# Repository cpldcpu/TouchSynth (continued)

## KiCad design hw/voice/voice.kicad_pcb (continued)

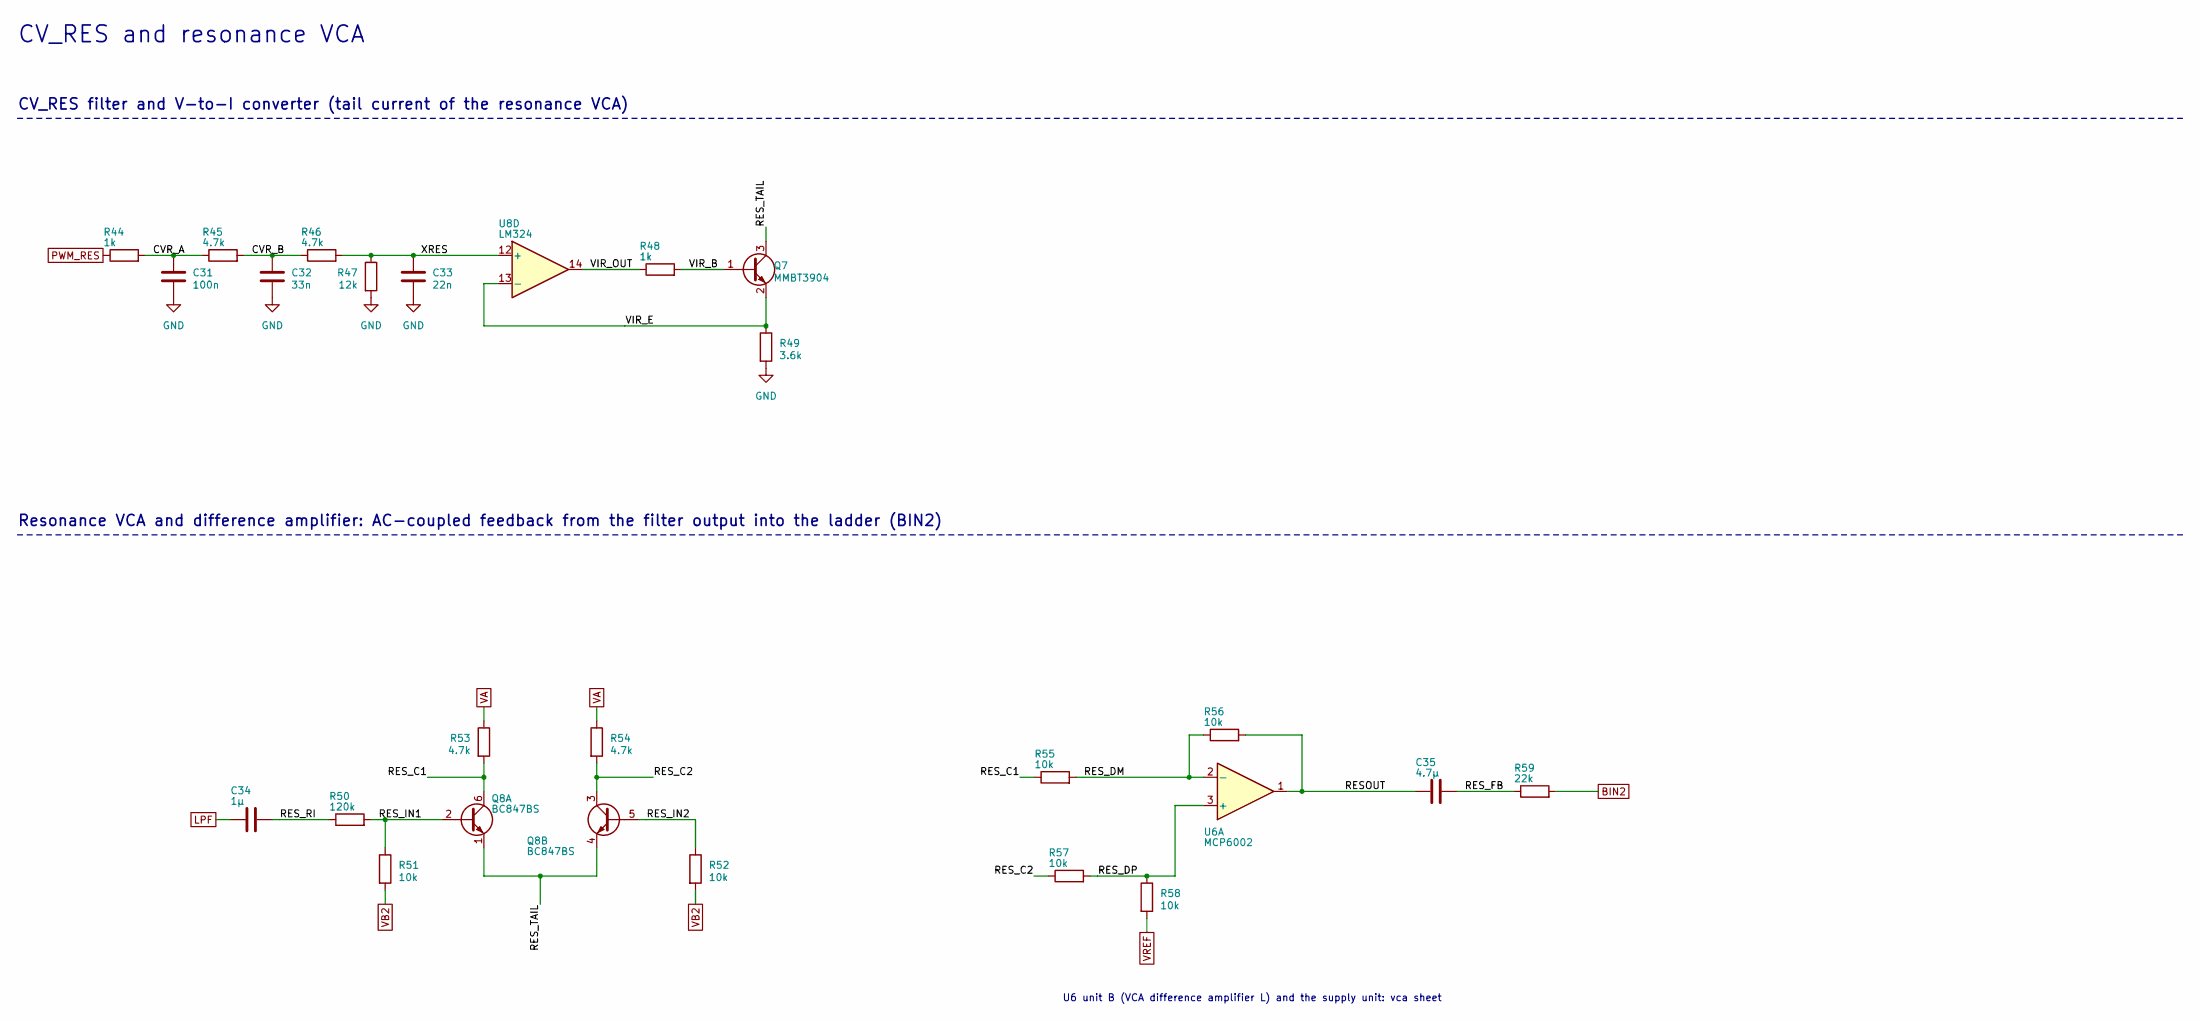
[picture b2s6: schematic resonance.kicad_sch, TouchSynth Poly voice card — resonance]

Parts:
C31: 100n; C_0402_1005Metric; LCSC C1525
C32: 33n; C_0603_1608Metric; LCSC C21117
C33: 22n; C_0402_1005Metric; LCSC C1532
C34: 1µ; C_0402_1005Metric; LCSC C52923
C35: 4.7µ; C_0402_1005Metric; LCSC C23733
Q7: MMBT3904; SOT-23; LCSC C20526
Q8: BC847BS; SOT-363_SC-70-6; LCSC C41375126
R44, R48: 1k; R_0402_1005Metric; LCSC C11702
R45, R46, R53, R54: 4.7k; R_0402_1005Metric; LCSC C25900
R47: 12k; R_0402_1005Metric; LCSC C25752
R49: 3.6k; R_0603_1608Metric; LCSC C22980
R50: 120k; R_0402_1005Metric; LCSC C25750
R51, R52, R55, R56, R57, R58: 10k; R_0402_1005Metric; LCSC C25744
R59: 22k; R_0402_1005Metric; LCSC C25768
U6: MCP6002; SOIC-8_3.9x4.9mm_P1.27mm; LCSC C7377
U8: LM324; SOIC-14_3.9x8.7mm_P1.27mm; LCSC C71035

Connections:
/resonance/CVR_A: C31.1, R44.2, R45.1
/resonance/CVR_B: C32.1, R45.2, R46.1
/resonance/RESOUT: C35.1, R56.2, U6.1
/resonance/RES_C1: Q8.6 (C1), R53.2, R55.1
/resonance/RES_C2: Q8.3 (C2), R54.2, R57.1
/resonance/RES_DM: R55.2, R56.1, U6.2 (-)
/resonance/RES_DP: R57.2, R58.1, U6.3 (+)
/resonance/RES_FB: C35.2, R59.1
/resonance/RES_IN1: Q8.2 (B1), R50.2, R51.1
/resonance/RES_IN2: Q8.5 (B2), R52.1
/resonance/RES_RI: C34.2, R50.1
/resonance/RES_TAIL: Q7.3 (C), Q8.1 (E1), Q8.4 (E2)
/resonance/VIR_B: Q7.1 (B), R48.2
/resonance/VIR_E: Q7.2 (E), R49.1, U8.13 (-)
/resonance/VIR_OUT: R48.1, U8.14
/resonance/XRES: C33.1, R46.2, R47.1, U8.12 (+)
BIN2: R59.2; also elsewhere on the board
GND: C31.2, C32.2, C33.2, R47.2, R49.2; also elsewhere on the board
LPF: C34.1; also elsewhere on the board
PWM_RES: R44.1; also elsewhere on the board
VA: R53.1, R54.1; also elsewhere on the board
VB2: R51.2, R52.2; also elsewhere on the board
VREF: R58.2; also elsewhere on the board

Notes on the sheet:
CV_RES and resonance VCA
CV_RES filter and V-to-I converter (tail current of the resonance VCA)
Resonance VCA and difference amplifier: AC-coupled feedback from the filter output into the ladder (BIN2)
U6 unit B (VCA difference amplifier L) and the supply unit: vca sheet

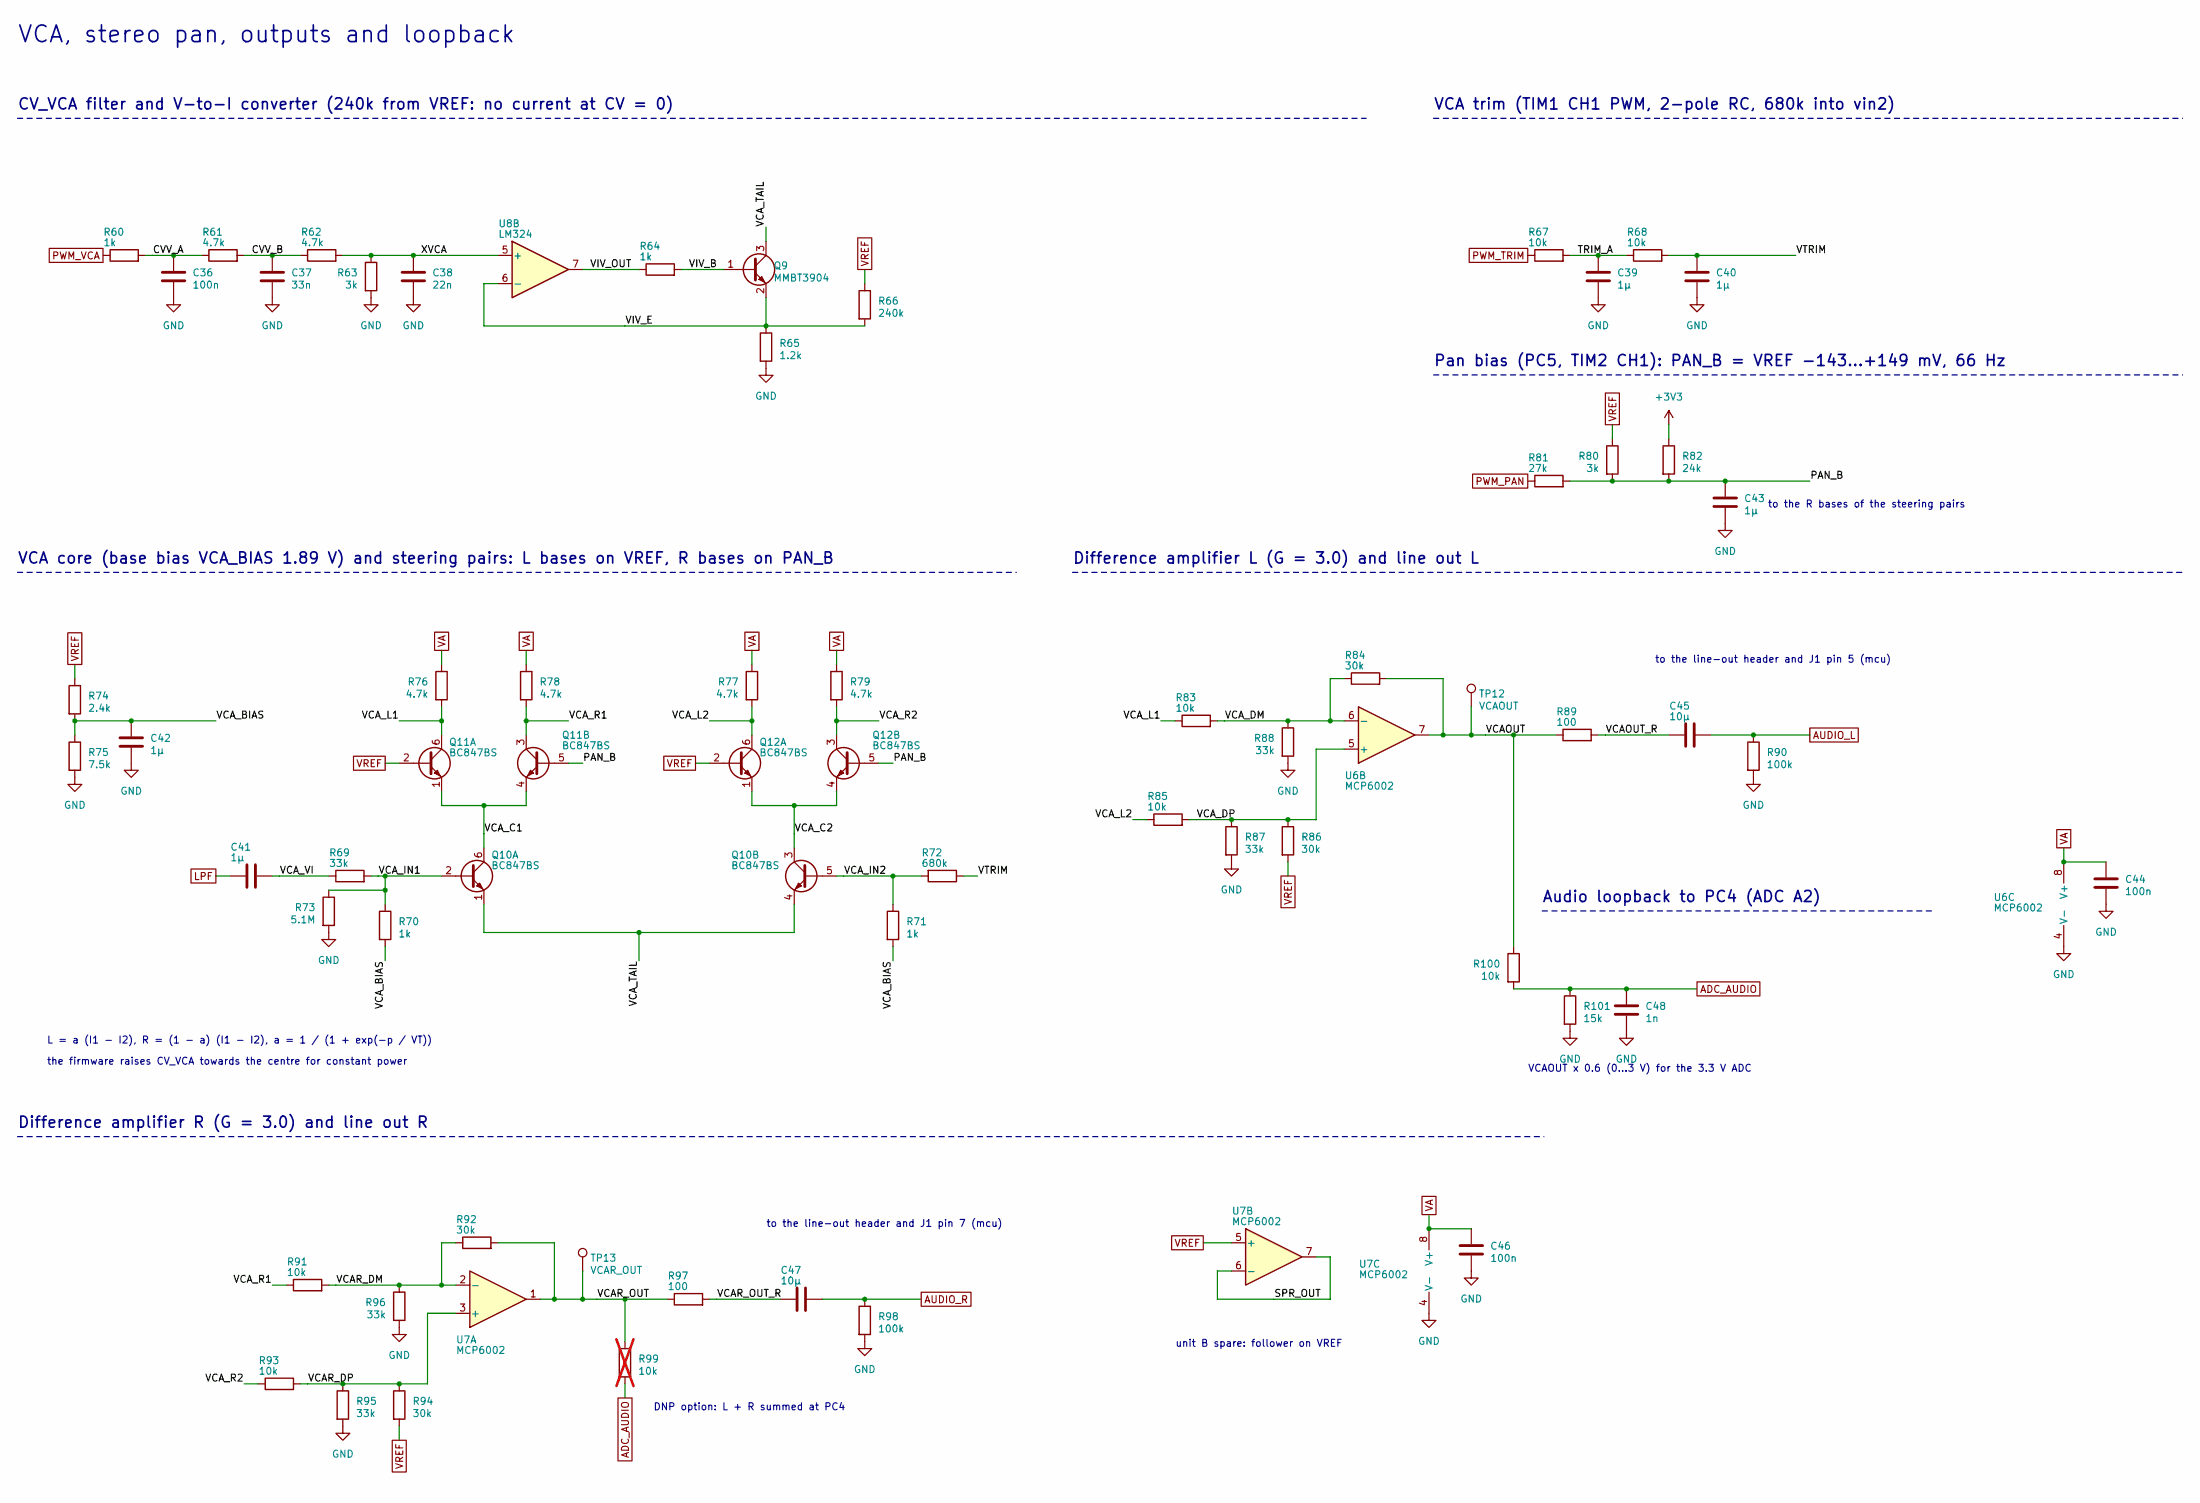
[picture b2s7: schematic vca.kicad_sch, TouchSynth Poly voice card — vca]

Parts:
C36, C44, C46: 100n; C_0402_1005Metric; LCSC C1525
C37: 33n; C_0603_1608Metric; LCSC C21117
C38: 22n; C_0402_1005Metric; LCSC C1532
C39, C40, C41, C42, C43: 1µ; C_0402_1005Metric; LCSC C52923
C45, C47: 10µ; C_0402_1005Metric; LCSC C15525
C48: 1n; C_0402_1005Metric; LCSC C1523
Q9: MMBT3904; SOT-23; LCSC C20526
Q10, Q11, Q12: BC847BS; SOT-363_SC-70-6; LCSC C41375126
R60, R64, R70, R71: 1k; R_0402_1005Metric; LCSC C11702
R61, R62, R76, R77, R78, R79: 4.7k; R_0402_1005Metric; LCSC C25900
R63, R80: 3k; R_0603_1608Metric; LCSC C4211
R65: 1.2k; R_0402_1005Metric; LCSC C25862
R66: 240k; R_0603_1608Metric; LCSC C4197
R67, R68, R83, R85, R91, R93, R100: 10k; R_0402_1005Metric; LCSC C25744
R69, R87, R88, R95, R96: 33k; R_0402_1005Metric; LCSC C25779
R72: 680k; R_0603_1608Metric; LCSC C25822
R73: 5.1M; R_0603_1608Metric; LCSC C13320
R74: 2.4k; R_0402_1005Metric; LCSC C25882
R75: 7.5k; R_0402_1005Metric; LCSC C25918
R81: 27k; R_0402_1005Metric; LCSC C25771
R82: 24k; R_0402_1005Metric; LCSC C25769
R84, R86, R92, R94: 30k; R_0603_1608Metric; LCSC C22984
R89, R97: 100; R_0402_1005Metric; LCSC C25076
R90, R98: 100k; R_0402_1005Metric; LCSC C25741
R99: 10k; R_0402_1005Metric; LCSC C25744; not fitted
R101: 15k; R_0402_1005Metric; LCSC C25756
TP12: VCAOUT; TestPoint_Pad_D1.0mm
TP13: VCAR_OUT; TestPoint_Pad_D1.0mm
U6, U7: MCP6002; SOIC-8_3.9x4.9mm_P1.27mm; LCSC C7377
U8: LM324; SOIC-14_3.9x8.7mm_P1.27mm; LCSC C71035

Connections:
+3V3: R82.1; also elsewhere on the board
/vca/CVV_A: C36.1, R60.2, R61.1
/vca/CVV_B: C37.1, R61.2, R62.1
/vca/PAN_B: C43.1, Q11.5 (B2), Q12.5 (B2), R80.2, R81.2, R82.2
/vca/SPR_OUT: U7.6 (-), U7.7
/vca/TRIM_A: C39.1, R67.2, R68.1
/vca/VCAOUT: R84.2, R89.1, R100.1, TP12.1, U6.7
/vca/VCAOUT_R: C45.1, R89.2
/vca/VCAR_DM: R91.2, R92.1, R96.1, U7.2 (-)
/vca/VCAR_DP: R93.2, R94.1, R95.1, U7.3 (+)
/vca/VCAR_OUT: R92.2, R97.1, R99.1, TP13.1, U7.1
/vca/VCAR_OUT_R: C47.1, R97.2
/vca/VCA_BIAS: C42.1, R70.2, R71.2, R74.2, R75.1
/vca/VCA_C1: Q10.6 (C1), Q11.1 (E1), Q11.4 (E2)
/vca/VCA_C2: Q10.3 (C2), Q12.1 (E1), Q12.4 (E2)
/vca/VCA_DM: R83.2, R84.1, R88.1, U6.6 (-)
/vca/VCA_DP: R85.2, R86.1, R87.1, U6.5 (+)
/vca/VCA_IN1: Q10.2 (B1), R69.2, R70.1, R73.1
/vca/VCA_IN2: Q10.5 (B2), R71.1, R72.2
/vca/VCA_L1: Q11.6 (C1), R76.2, R83.1
/vca/VCA_L2: Q12.6 (C1), R77.2, R85.1
/vca/VCA_R1: Q11.3 (C2), R78.2, R91.1
/vca/VCA_R2: Q12.3 (C2), R79.2, R93.1
/vca/VCA_TAIL: Q9.3 (C), Q10.1 (E1), Q10.4 (E2)
/vca/VCA_VI: C41.2, R69.1
/vca/VIV_B: Q9.1 (B), R64.2
/vca/VIV_E: Q9.2 (E), R65.1, R66.2, U8.6 (-)
/vca/VIV_OUT: R64.1, U8.7
/vca/VTRIM: C40.1, R68.2, R72.1
/vca/XVCA: C38.1, R62.2, R63.1, U8.5 (+)
ADC_AUDIO: C48.1, R99.2, R100.2, R101.1; also elsewhere on the board
AUDIO_L: C45.2, R90.1; also elsewhere on the board
AUDIO_R: C47.2, R98.1; also elsewhere on the board
GND: C36.2, C37.2, C38.2, C39.2, C40.2, C42.2, C43.2, C44.2, C46.2, C48.2, R63.2, R65.2, R73.2, R75.2, R87.2, R88.2, R90.2, R95.2, R96.2, R98.2, R101.2, U6.4 (V-), U7.4 (V-); also elsewhere on the board
LPF: C41.1; also elsewhere on the board
PWM_PAN: R81.1; also elsewhere on the board
PWM_TRIM: R67.1; also elsewhere on the board
PWM_VCA: R60.1; also elsewhere on the board
VA: C44.1, C46.1, R76.1, R77.1, R78.1, R79.1, U6.8 (V+), U7.8 (V+); also elsewhere on the board
VREF: Q11.2 (B1), Q12.2 (B1), R66.1, R74.1, R80.1, R86.2, R94.2, U7.5 (+); also elsewhere on the board

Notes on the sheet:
VCA, stereo pan, outputs and loopback
CV_VCA filter and V-to-I converter (240k from VREF: no current at CV = 0)
VCA trim (TIM1 CH1 PWM, 2-pole RC, 680k into vin2)
Pan bias (PC5, TIM2 CH1): PAN_B = VREF -143...+149 mV, 66 Hz
to the R bases of the steering pairs
VCA core (base bias VCA_BIAS 1.89 V) and steering pairs: L bases on VREF, R bases on PAN_B
L = a (I1 - I2), R = (1 - a) (I1 - I2), a = 1 / (1 + exp(-p / VT))
the firmware raises CV_VCA towards the centre for constant power
Difference amplifier L (G = 3.0) and line out L
to the line-out header and J1 pin 5 (mcu)
Audio loopback to PC4 (ADC A2)
VCAOUT x 0.6 (0...3 V) for the 3.3 V ADC
Difference amplifier R (G = 3.0) and line out R
to the line-out header and J1 pin 7 (mcu)
DNP option: L + R summed at PC4
unit B spare: follower on VREF

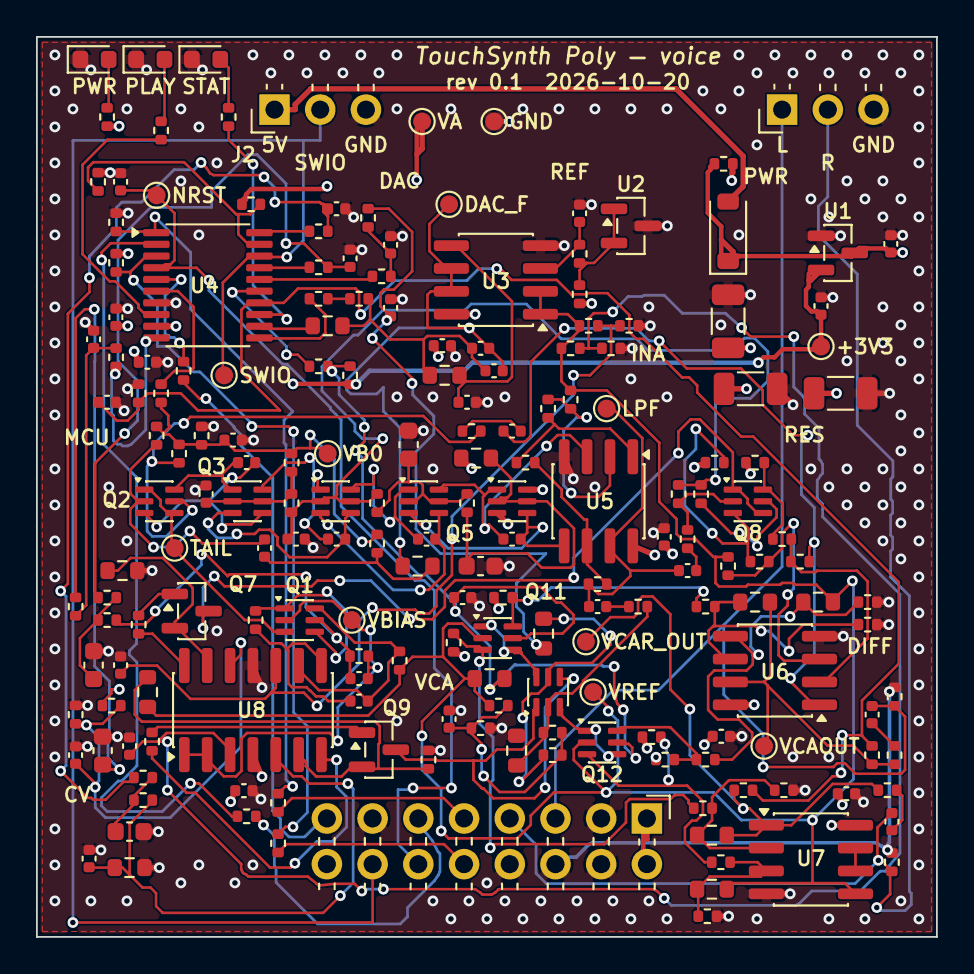
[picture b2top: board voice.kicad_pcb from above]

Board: 4 copper layers, 50.0 x 50.0 mm, 190 parts (0 on the bottom side), 114 nets.

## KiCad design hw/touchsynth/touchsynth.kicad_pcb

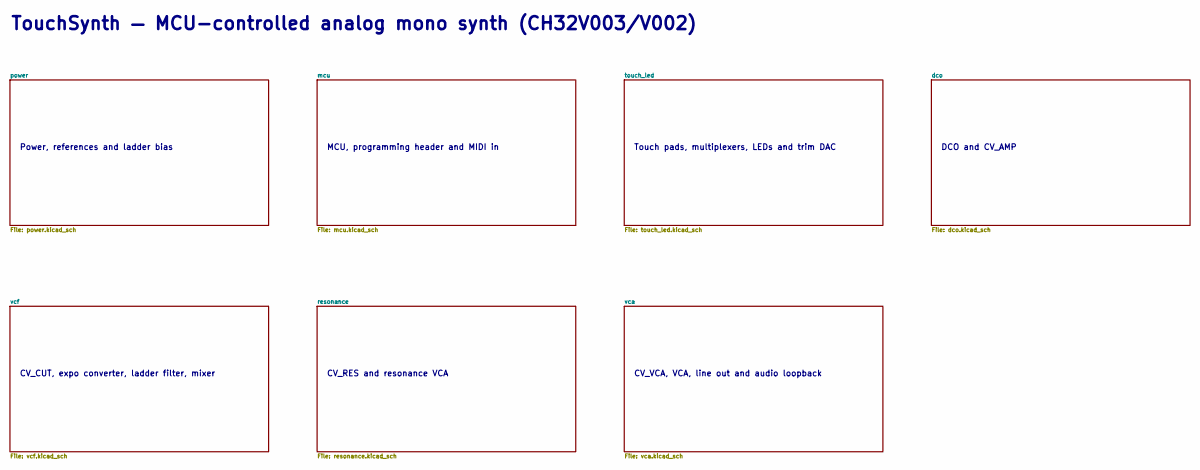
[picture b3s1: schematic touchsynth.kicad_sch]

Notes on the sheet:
Power, references and ladder bias
MCU, programming header and MIDI in
Touch pads, multiplexers, LEDs and trim DAC
DCO and CV_AMP
CV_CUT, expo converter, ladder filter, mixer
CV_RES and resonance VCA
CV_VCA, VCA, line out and audio loopback
TouchSynth — MCU-controlled analog mono synth (CH32V003/V002)

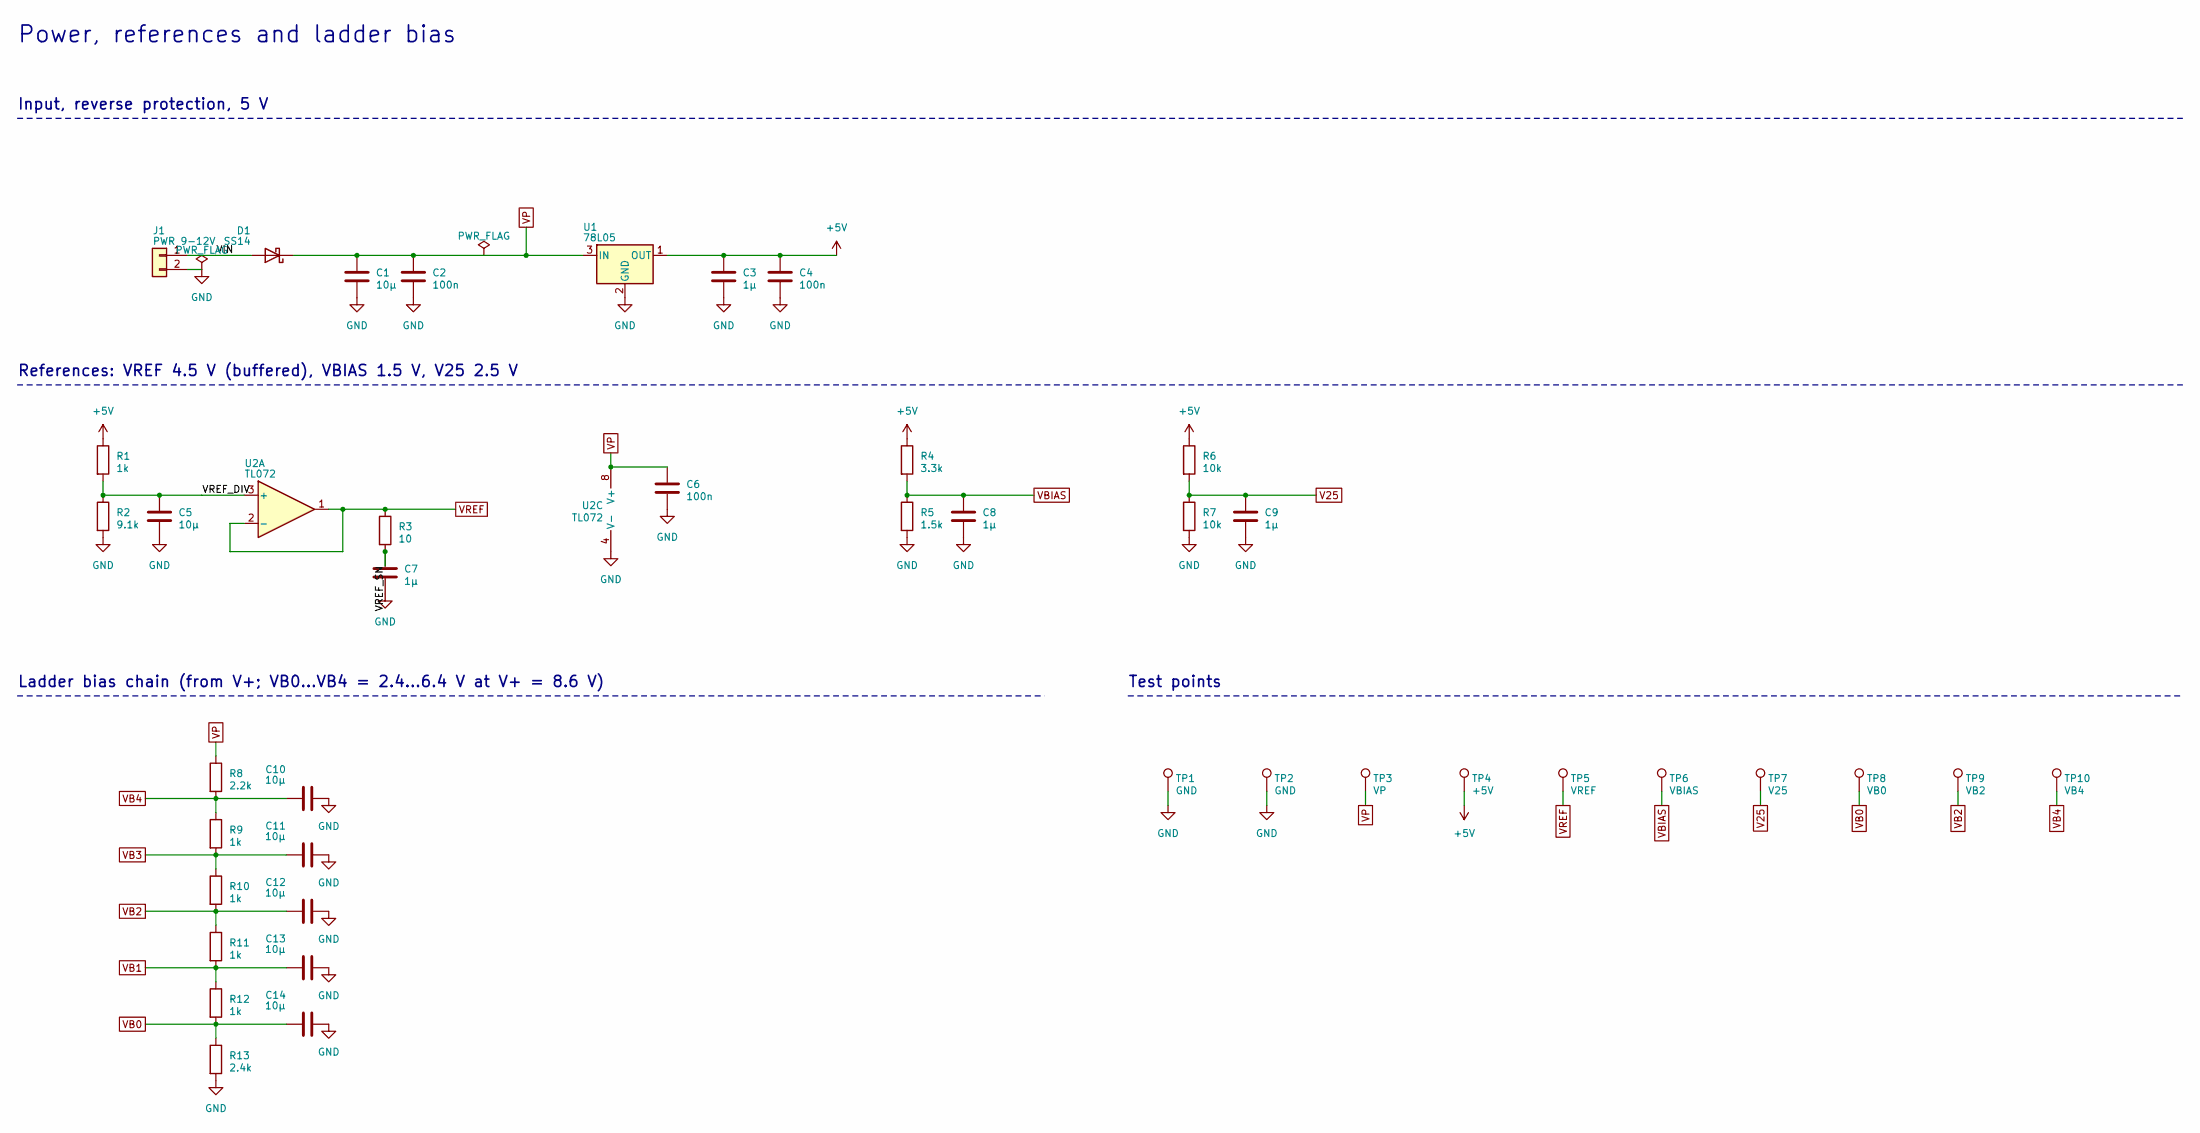
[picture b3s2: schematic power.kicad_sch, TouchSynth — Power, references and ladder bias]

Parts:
C1, C10, C11, C12, C13: 10µ; C_0603_1608Metric; LCSC C96446
C2, C4, C6: 100n; C_0603_1608Metric; LCSC C14663
C3, C7, C8, C9: 1µ; C_0603_1608Metric; LCSC C15849
C5, C14: 10µ; C_0603_1608Metric; LCSC C19702
D1: SS14; D_SMA; LCSC C2480
J1: PWR 9-12V; PinHeader_1x02_P2.54mm_Vertical
R1, R9, R10, R11, R12: 1k; R_0603_1608Metric; LCSC C21190
R2: 9.1k; R_0603_1608Metric; LCSC C23260
R3: 10; R_0603_1608Metric; LCSC C22859
R4: 3.3k; R_0603_1608Metric; LCSC C22978
R5: 1.5k; R_0603_1608Metric; LCSC C22843
R6, R7: 10k; R_0603_1608Metric; LCSC C25804
R8: 2.2k; R_0603_1608Metric; LCSC C4190
R13: 2.4k; R_0603_1608Metric; LCSC C22940
TP1, TP2: GND; PinHeader_1x01_P2.54mm_Vertical
TP3: VP; TestPoint_Pad_D1.0mm
TP4: +5V; TestPoint_Pad_D1.0mm
TP5: VREF; TestPoint_Pad_D1.0mm
TP6: VBIAS; TestPoint_Pad_D1.0mm
TP7: V25; TestPoint_Pad_D1.0mm
TP8: VB0; TestPoint_Pad_D1.0mm
TP9: VB2; TestPoint_Pad_D1.0mm
TP10: VB4; TestPoint_Pad_D1.0mm
U1: 78L05; SOT-89-3; LCSC C71136
U2: TL072; SOIC-8_3.9x4.9mm_P1.27mm; LCSC C6961

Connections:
+5V: C3.1, C4.1, R1.1, R4.1, R6.1, TP4.1, U1.1 (OUT); also elsewhere on the board
/power/VIN: D1.2 (A), J1.1
/power/VREF_DIV: C5.1, R1.2, R2.1, U2.3 (+)
/power/VREF_SN: C7.1, R3.2
GND: C1.2, C2.2, C3.2, C4.2, C5.2, C6.2, C7.2, C8.2, C9.2, C10.2, C11.2, C12.2, C13.2, C14.2, J1.2, R2.2, R5.2, R7.2, R13.2, TP1.1, TP2.1, U1.2 (GND), U2.4 (V-); also elsewhere on the board
V25: C9.1, R6.2, R7.1, TP7.1; also elsewhere on the board
VB0: C14.1, R12.2, R13.1, TP8.1; also elsewhere on the board
VB1: C13.1, R11.2, R12.1; also elsewhere on the board
VB2: C12.1, R10.2, R11.1, TP9.1; also elsewhere on the board
VB3: C11.1, R9.2, R10.1; also elsewhere on the board
VB4: C10.1, R8.2, R9.1, TP10.1; also elsewhere on the board
VBIAS: C8.1, R4.2, R5.1, TP6.1; also elsewhere on the board
VP: C1.1, C2.1, C6.1, D1.1 (K), R8.1, TP3.1, U1.3 (IN), U2.8 (V+); also elsewhere on the board
VREF: R3.1, TP5.1, U2.1, U2.2 (-); also elsewhere on the board

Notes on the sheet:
Power, references and ladder bias
Input, reverse protection, 5 V
References: VREF 4.5 V (buffered), VBIAS 1.5 V, V25 2.5 V
Ladder bias chain (from V+; VB0...VB4 = 2.4...6.4 V at V+ = 8.6 V)
Test points

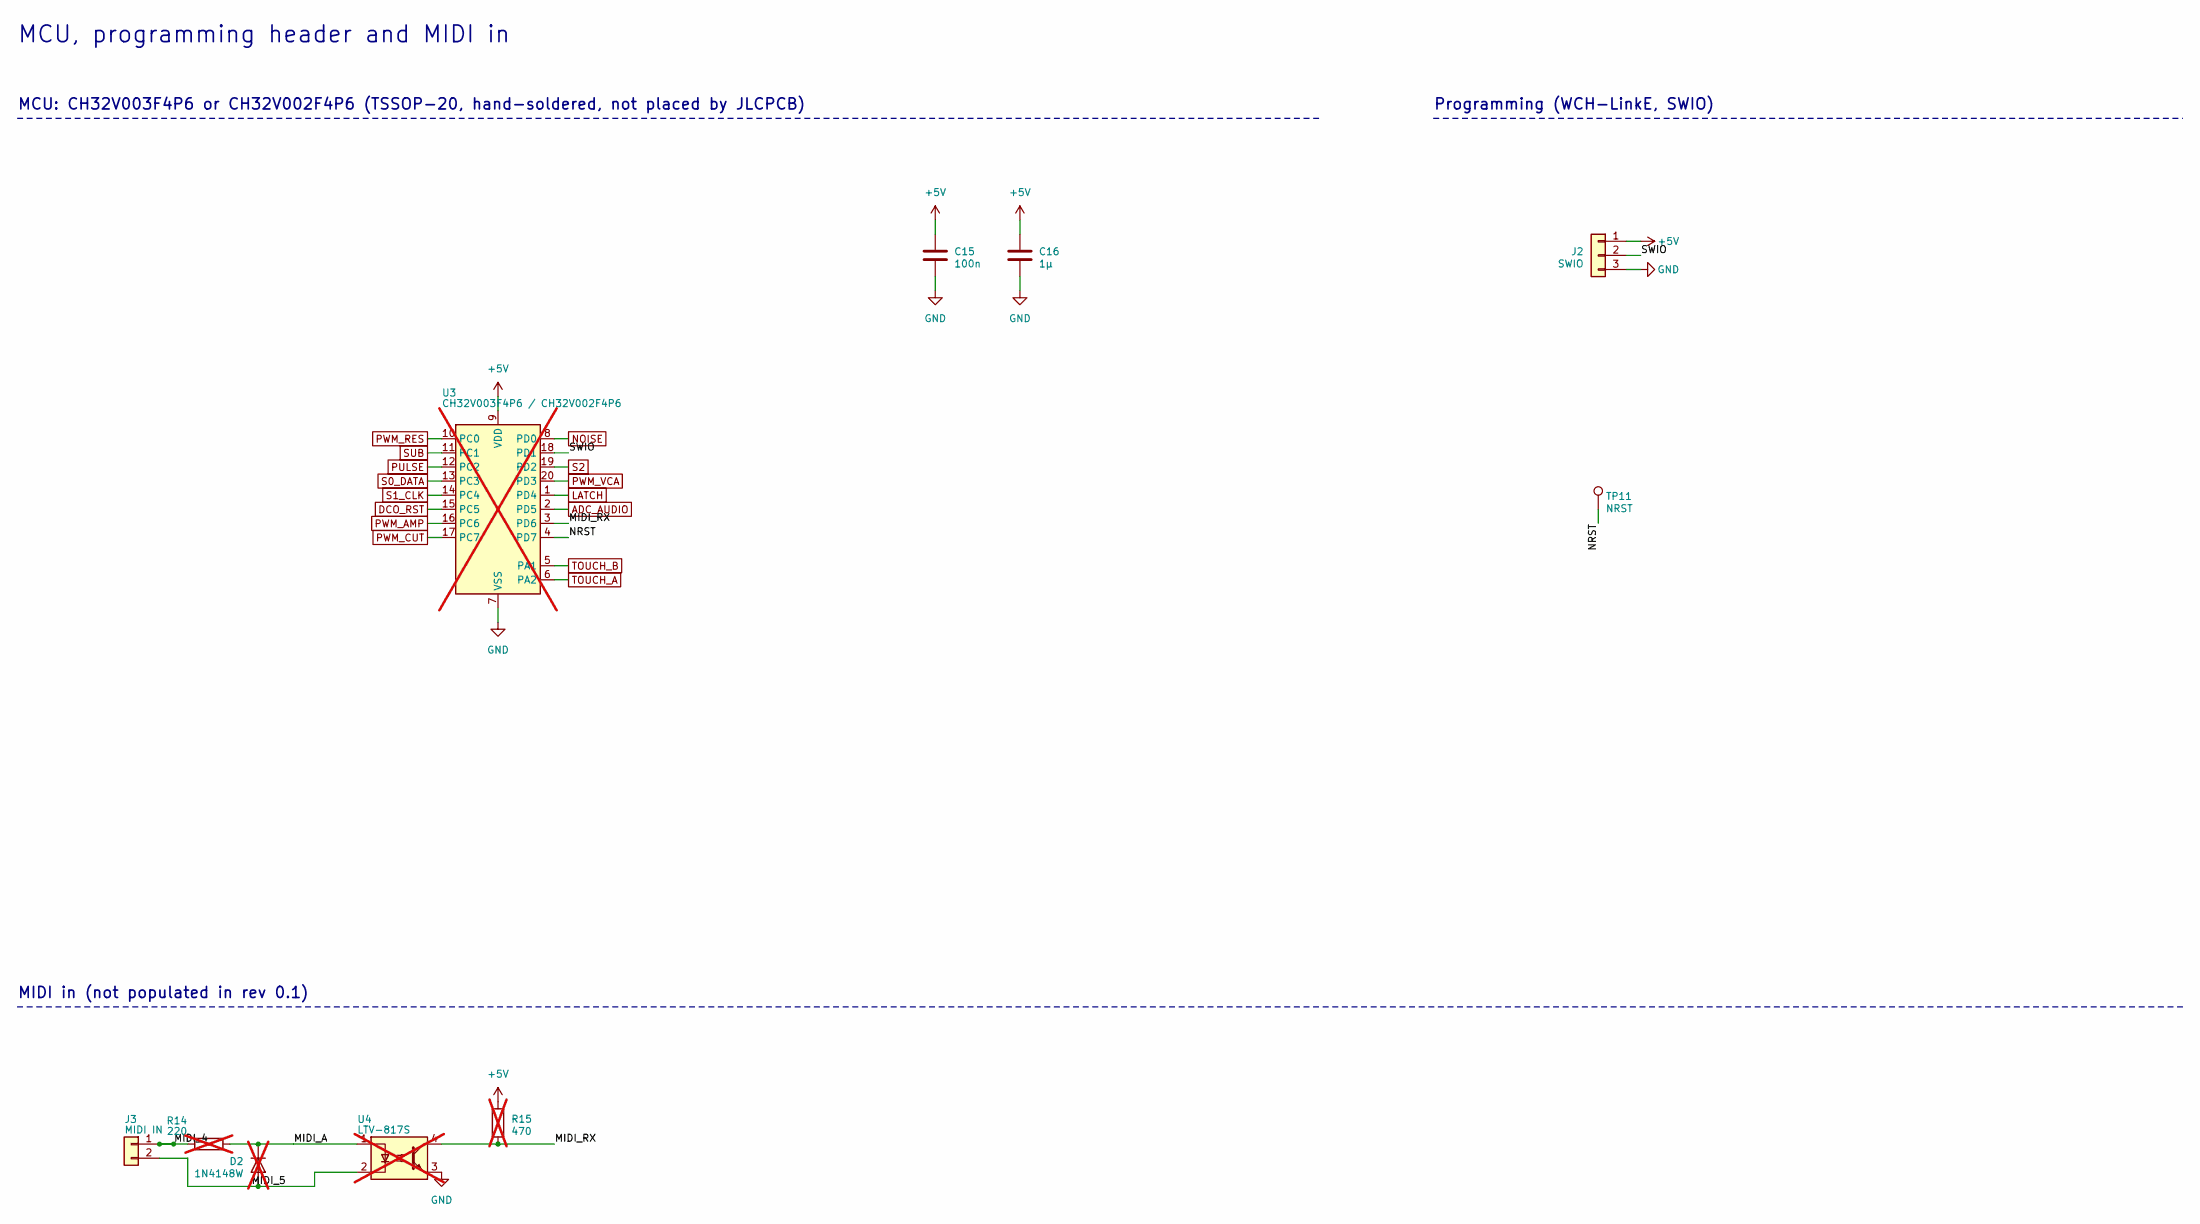
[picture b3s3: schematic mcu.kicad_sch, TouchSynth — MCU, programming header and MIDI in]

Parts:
C15: 100n; C_0603_1608Metric; LCSC C14663
C16: 1µ; C_0603_1608Metric; LCSC C15849
D2: 1N4148W; D_SOD-123; LCSC C81598; not fitted
J2: SWIO; PinHeader_1x03_P2.54mm_Vertical
J3: MIDI IN; PinHeader_1x02_P2.54mm_Vertical
R14: 220; R_0603_1608Metric; LCSC C22962; not fitted
R15: 470; R_0603_1608Metric; LCSC C23179; not fitted
TP11: NRST; TestPoint_Pad_D1.0mm
U3: CH32V003F4P6 / CH32V002F4P6; TSSOP-20_4.4x6.5mm_P0.65mm; not fitted
U4: LTV-817S; SMDIP-4_W9.53mm; LCSC C109227; not fitted

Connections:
+5V: C15.1, C16.1, J2.1, R15.1, U3.9 (VDD); also elsewhere on the board
/mcu/MIDI_4: J3.1, R14.1
/mcu/MIDI_5: D2.2 (A), J3.2, U4.2
/mcu/MIDI_A: D2.1 (K), R14.2, U4.1
/mcu/MIDI_RX: R15.2, U3.3 (PD6), U4.4
/mcu/NRST: TP11.1, U3.4 (PD7)
/mcu/SWIO: J2.2, U3.18 (PD1)
ADC_AUDIO: U3.2 (PD5); also elsewhere on the board
DCO_RST: U3.15 (PC5); also elsewhere on the board
GND: C15.2, C16.2, J2.3, U3.7 (VSS), U4.3; also elsewhere on the board
LATCH: U3.1 (PD4); also elsewhere on the board
NOISE: U3.8 (PD0); also elsewhere on the board
PULSE: U3.12 (PC2); also elsewhere on the board
PWM_AMP: U3.16 (PC6); also elsewhere on the board
PWM_CUT: U3.17 (PC7); also elsewhere on the board
PWM_RES: U3.10 (PC0); also elsewhere on the board
PWM_VCA: U3.20 (PD3); also elsewhere on the board
S0_DATA: U3.13 (PC3); also elsewhere on the board
S1_CLK: U3.14 (PC4); also elsewhere on the board
S2: U3.19 (PD2); also elsewhere on the board
SUB: U3.11 (PC1); also elsewhere on the board
TOUCH_A: U3.6 (PA2); also elsewhere on the board
TOUCH_B: U3.5 (PA1); also elsewhere on the board

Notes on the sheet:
MCU, programming header and MIDI in
MCU: CH32V003F4P6 or CH32V002F4P6 (TSSOP-20, hand-soldered, not placed by JLCPCB)
Programming (WCH-LinkE, SWIO)
MIDI in (not populated in rev 0.1)
